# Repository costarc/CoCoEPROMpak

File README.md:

# CoCoEPROMpak

## 📖 The Book

This project is **Chapter 7, "CoCo EPROM Pak"**, in a book:

**Chips, Code, and Cartridges: Turn Curiosity into Creation with 13 Hands-On Projects, from 8-bit Classics to FPGAs**

It walks through thirteen of my own hardware and software projects, from 8-bit classics to FPGAs, for beginners and curious makers. Each chapter explains how one project works and how to build it, with colour diagrams and real code from its repository.

### 👉 [Get the book on Amazon](https://link.amazon/B013Yaq9y)

<sub>As an Amazon Associate, the author earns from qualifying purchases. Buying through this link
supports these projects at no extra cost to you.</sub>

## Writing the ROM from the CoCo

The AT28C256 version can be programmed while it sits in the CoCo, with no programmer. The writer, the PC
tool that prepares ROM images and its tests are in [`Software/EEWRITE`](Software/EEWRITE). It needs the
/OE modification described there and in the book.

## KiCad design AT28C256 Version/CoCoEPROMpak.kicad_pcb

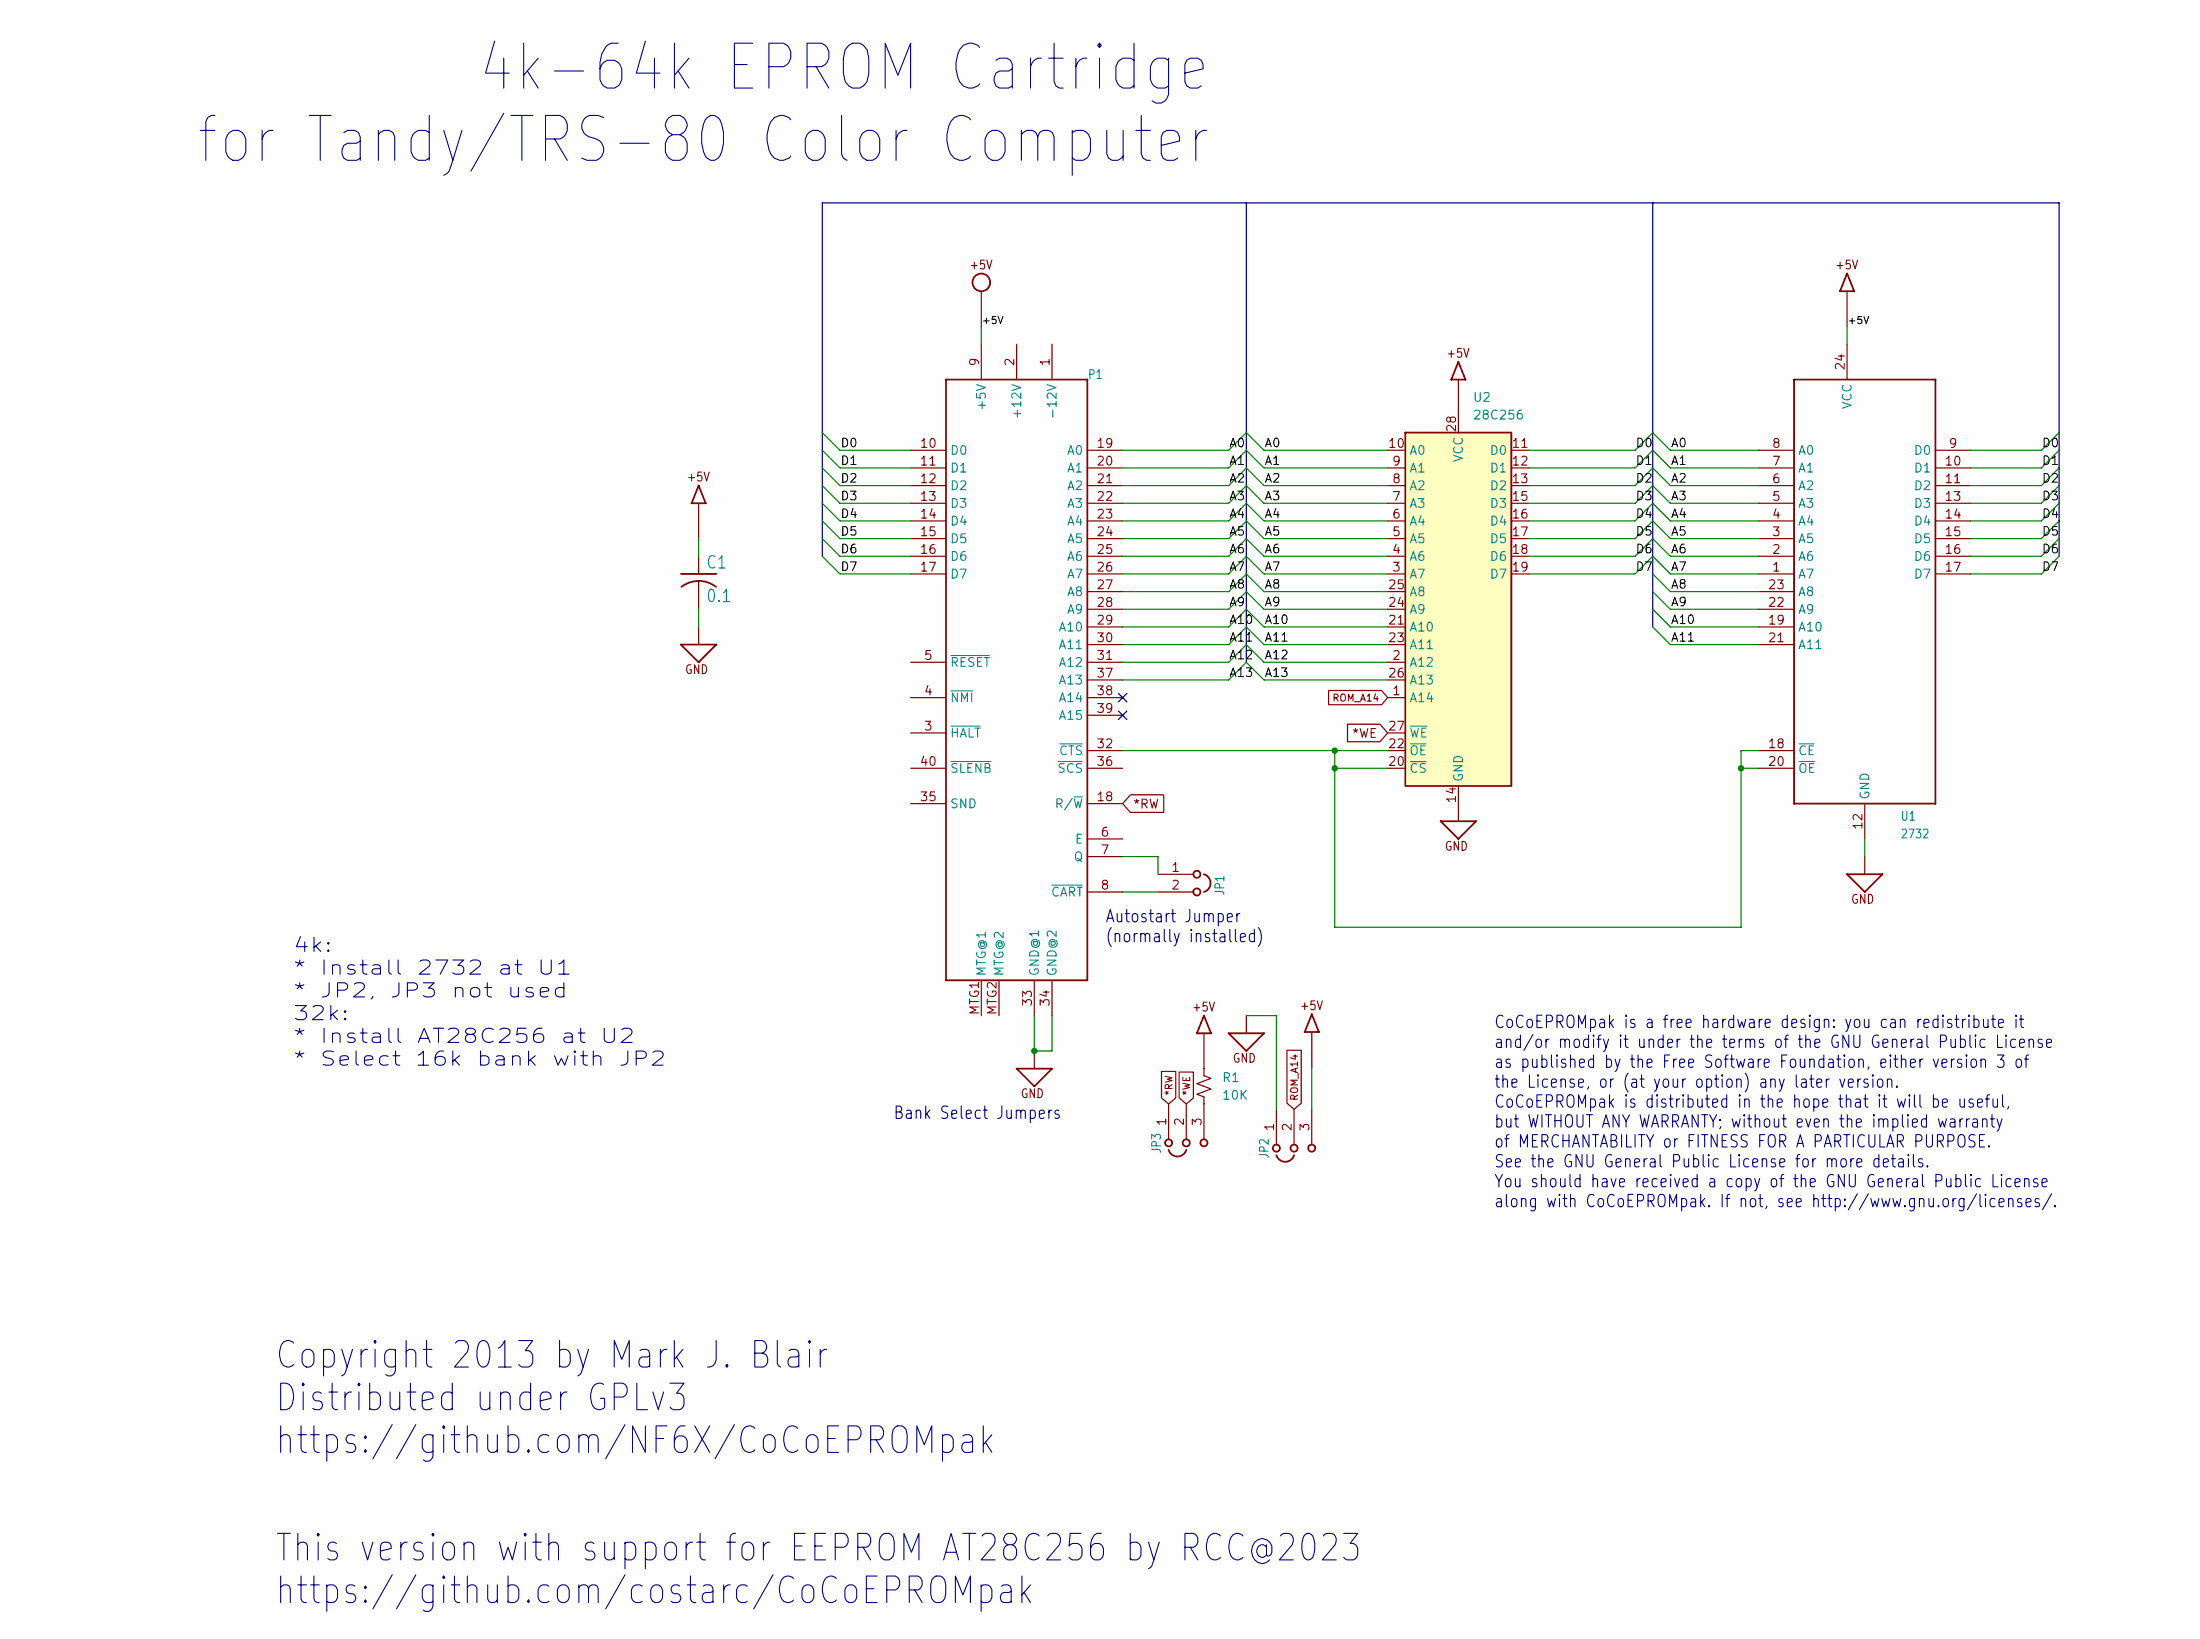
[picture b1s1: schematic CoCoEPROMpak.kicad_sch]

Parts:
C1: 0.1; C050-025X075
JP1: JP2; JP2-100MIL
JP2, JP3: JP3; JP3-100MIL
P1: COCO-CART; COCO-CART-2.1X1.75
R1: 10K; R_Axial_DIN0207_L6.3mm_D2.5mm_P7.62mm_Horizontal
U1: 2732; DIL24
U2: 28C256; DIP-28_W15.24mm

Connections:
*RW: JP3.1, P1.18 (R/~W)
*WE: JP3.2, U2.27 (~WE)
+5V: C1.1, JP2.3, P1.9 (+5V), R1.1, U1.24 (VCC), U2.28 (VCC)
/A0: P1.19 (A0), U1.8 (A0), U2.10 (A0)
/A1: P1.20 (A1), U1.7 (A1), U2.9 (A1)
/A2: P1.21 (A2), U1.6 (A2), U2.8 (A2)
/A3: P1.22 (A3), U1.5 (A3), U2.7 (A3)
/A4: P1.23 (A4), U1.4 (A4), U2.6 (A4)
/A5: P1.24 (A5), U1.3 (A5), U2.5 (A5)
/A6: P1.25 (A6), U1.2 (A6), U2.4 (A6)
/A7: P1.26 (A7), U1.1 (A7), U2.3 (A7)
/A8: P1.27 (A8), U1.23 (A8), U2.25 (A8)
/A9: P1.28 (A9), U1.22 (A9), U2.24 (A9)
/A10: P1.29 (A10), U1.19 (A10), U2.21 (A10)
/A11: P1.30 (A11), U1.21 (A11), U2.23 (A11)
/A12: P1.31 (A12), U2.2 (A12)
/A13: P1.37 (A13), U2.26 (A13)
/D0: P1.10 (D0), U1.9 (D0), U2.11 (D0)
/D1: P1.11 (D1), U1.10 (D1), U2.12 (D1)
/D2: P1.12 (D2), U1.11 (D2), U2.13 (D2)
/D3: P1.13 (D3), U1.13 (D3), U2.15 (D3)
/D4: P1.14 (D4), U1.14 (D4), U2.16 (D4)
/D5: P1.15 (D5), U1.15 (D5), U2.17 (D5)
/D6: P1.16 (D6), U1.16 (D6), U2.18 (D6)
/D7: P1.17 (D7), U1.17 (D7), U2.19 (D7)
GND: C1.2, JP2.1, P1.33 (GND@1), P1.34 (GND@2), U1.12 (GND), U2.14 (GND)
unnamed: JP1.1, P1.7 (Q)
unnamed: JP1.2, P1.8 (~CART)
unnamed: JP3.3, R1.2
unnamed: P1.32 (~CTS), U1.18 (~CE), U1.20 (~OE), U2.20 (~CS), U2.22 (~OE)
ROM_A14: JP2.2, U2.1 (A14)

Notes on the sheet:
4k-64k EPROM Cartridge for Tandy/TRS-80 Color Computer
This version with support for EEPROM AT28C256 by RCC@2023 https://github.com/costarc/CoCoEPROMpak
4k: * Install 2732 at U1 * JP2, JP3 not used 32k: * Install AT28C256 at U2 * Select 16k bank with JP2
Bank Select Jumpers
CoCoEPROMpak is a free hardware design: you can redistribute it and/or modify it under the terms of the GNU General Public License as published by the Free Software Foundation, either version 3 of the License, or (at your option) any later version. CoCoEPROMpak is distributed in the hope that it wi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
Autostart Jumper (normally installed)
Copyright 2013 by Mark J. Blair Distributed under GPLv3 https://github.com/NF6X/CoCoEPROMpak

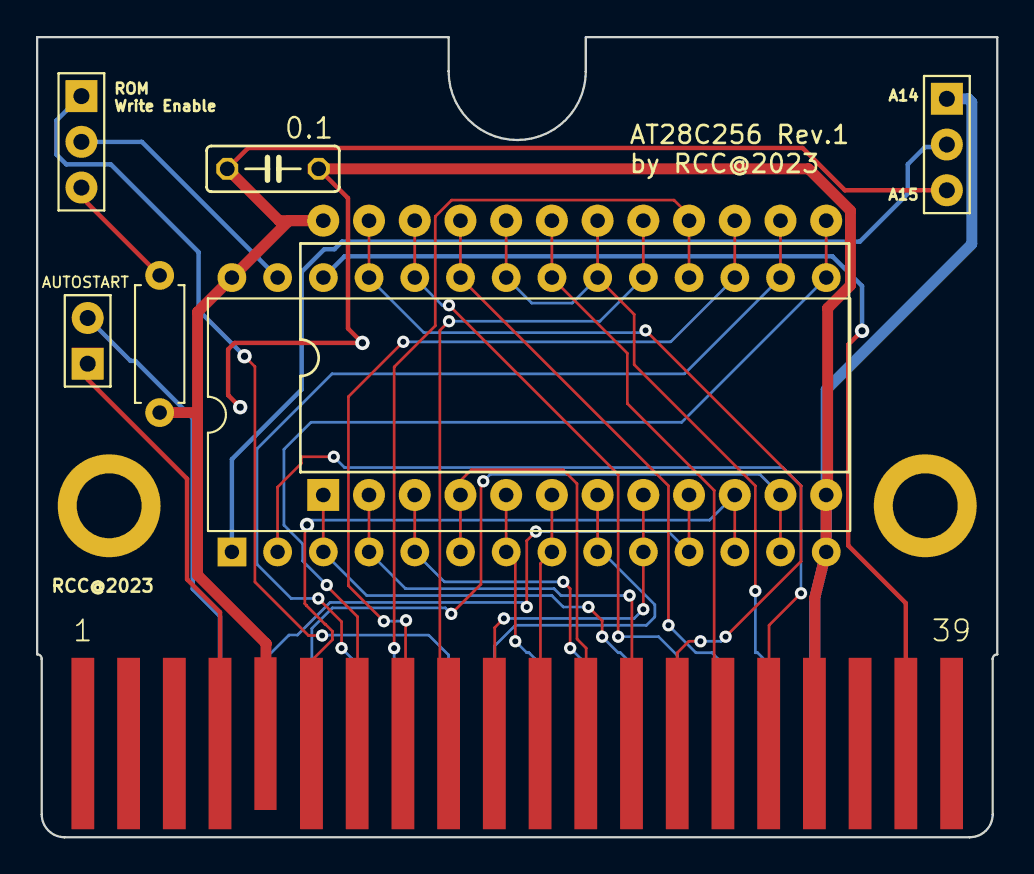
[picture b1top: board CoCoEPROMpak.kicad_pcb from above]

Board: 2 copper layers, 53.3 x 44.5 mm, 8 parts (0 on the bottom side), 31 nets.

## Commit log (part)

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2023-01-15 Added new version in Kicad to support AT28C256
2023-01-15 Renamed Directories
2023-01-15 Added gerber files
2023-01-17 Added gerbers with gnd plane added
2023-01-17 Renamed gerber file to contain revision number
2023-01-24 Added 3d model / pictures of pcb
2023-02-12 Rev.1
2023-11-09 Saved as Kicad 7
